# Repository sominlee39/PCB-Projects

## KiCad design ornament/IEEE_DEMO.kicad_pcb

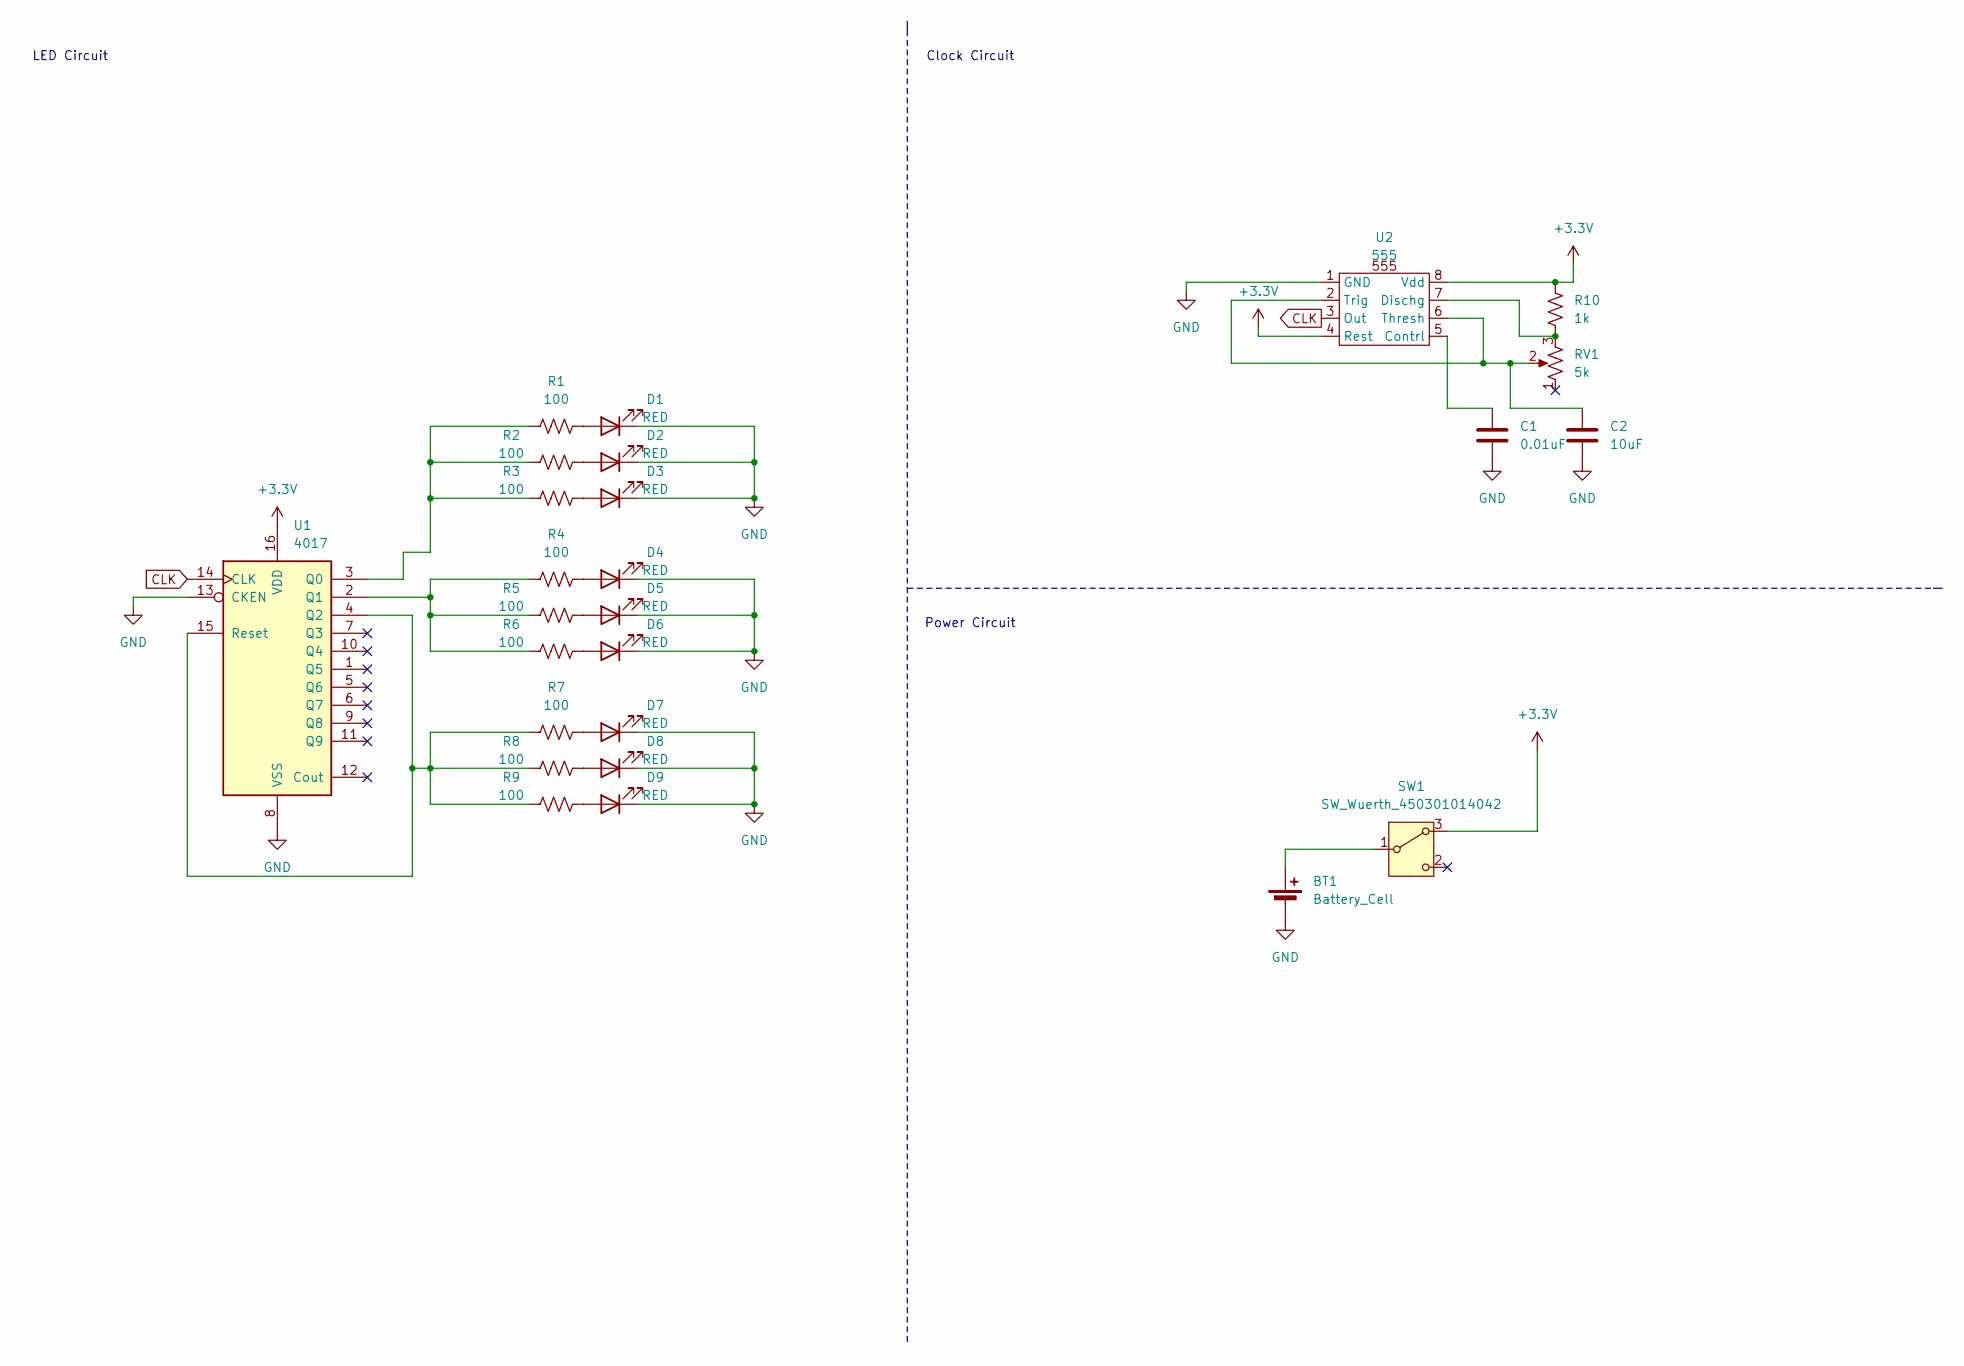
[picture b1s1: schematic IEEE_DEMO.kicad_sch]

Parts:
BT1: Battery_Cell; CR2025TR
C1: 0.01uF; CP_Radial_D5.0mm_P2.50mm
C2: 10uF; CP_Radial_D5.0mm_P2.50mm
D1, D2, D3, D4, D5, D6, D7, D8, D9: RED; LED_D3.0mm
R1, R2, R3, R4, R5, R6, R7, R8, R9: 100; R_0603_1608Metric_Pad0.98x0.95mm_HandSolder
R10: 1k; R_Axial_DIN0207_L6.3mm_D2.5mm_P7.62mm_Horizontal
RV1: 5k; CT6EP504
SW1: SW_Wuerth_450301014042
U1: 4017
U2: 555

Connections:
+3.3V: R10.1, SW1.3 (A), U1.16 (VDD), U2.4 (Rest), U2.8 (Vdd)
CLK: U1.14 (CLK), U2.3 (Out)
GND: BT1.2 (-), C1.2, C2.2, D1.1 (K), D2.1 (K), D3.1 (K), D4.1 (K), D5.1 (K), D6.1 (K), D7.1 (K), D8.1 (K), D9.1 (K), U1.8 (VSS), U1.13 (CKEN), U2.1 (GND)
unnamed: BT1.1 (+), SW1.1 (B)
unnamed: D1.2 (A), R1.2
unnamed: D2.2 (A), R2.2
unnamed: D3.2 (A), R3.2
unnamed: D4.2 (A), R4.2
unnamed: D5.2 (A), R5.2
unnamed: D6.2 (A), R6.2
unnamed: D7.2 (A), R7.2
unnamed: D8.2 (A), R8.2
unnamed: D9.2 (A), R9.2
unnamed: R1.1, R2.1, R3.1, U1.3 (Q0)
unnamed: R4.1, R5.1, R6.1, U1.2 (Q1)
unnamed: R7.1, R8.1, R9.1, U1.4 (Q2), U1.15 (Reset)
unnamed: C1.1, U2.5 (Contrl)
unnamed: R10.2, RV1.3, U2.7 (Dischg)
unnamed: C2.1, RV1.2, U2.2 (Trig), U2.6 (Thresh)

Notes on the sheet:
Power Circuit
Clock Circuit
LED Circuit

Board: 2 copper layers, 26 parts (0 on the bottom side), 19 nets, no tracks yet.

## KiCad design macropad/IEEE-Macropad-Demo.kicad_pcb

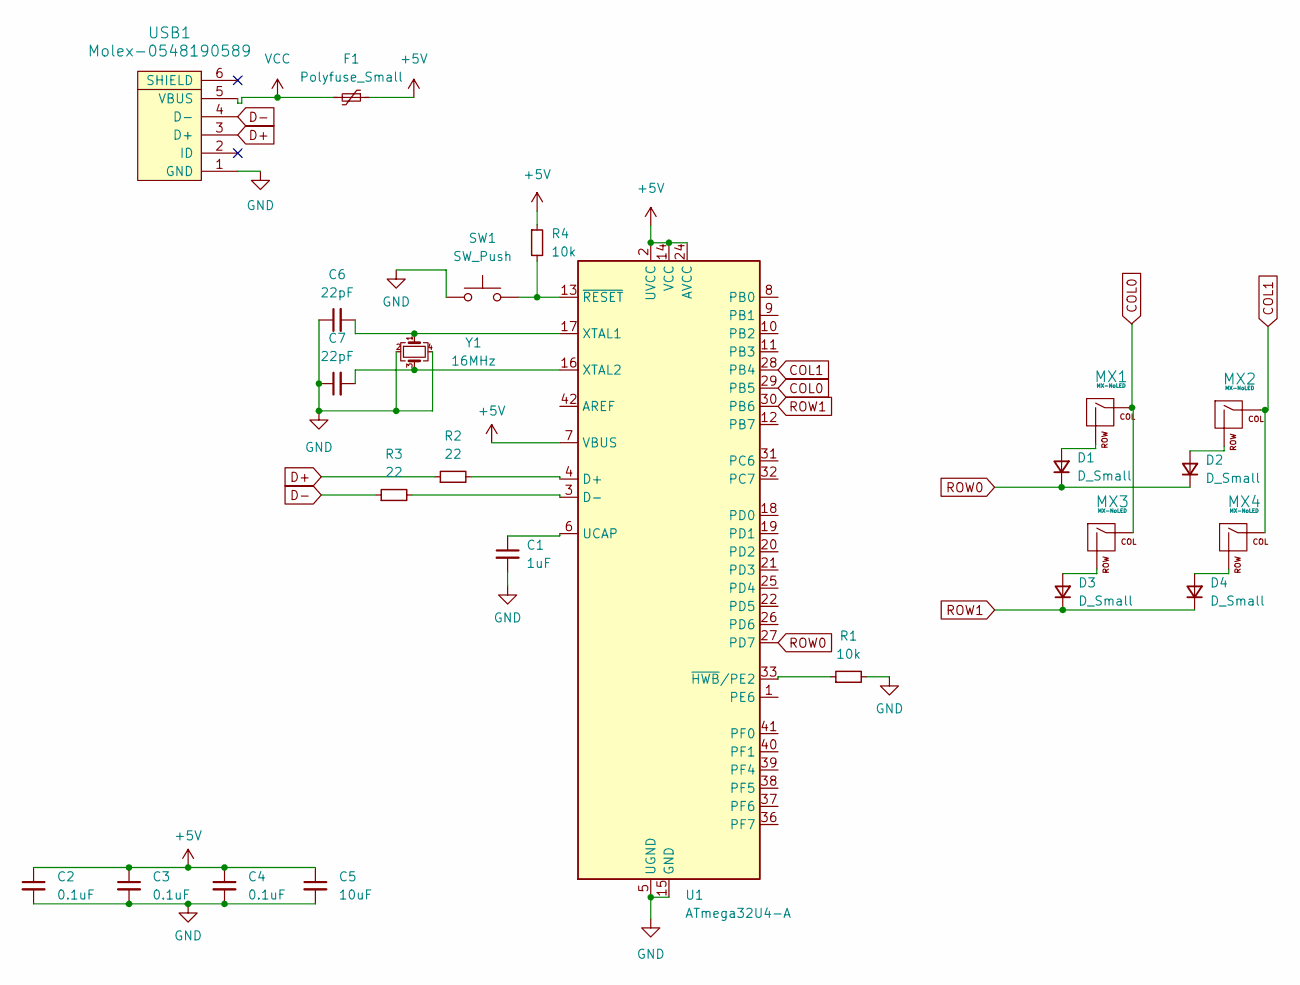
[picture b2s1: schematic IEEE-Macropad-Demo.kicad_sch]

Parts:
C1: 1uF; C_0805_2012Metric
C2, C3, C4: 0.1uF; C_0805_2012Metric
C5: 10uF; C_0805_2012Metric
C6, C7: 22pF; C_0805_2012Metric
D1, D2, D3, D4: D_Small; D_SOD-123
F1: Polyfuse_Small; Fuse_1206_3216Metric
MX1, MX2, MX3, MX4: MX-NoLED; MXOnly-1U-NoLED
R1, R4: 10k; R_0805_2012Metric
R2, R3: 22; R_0805_2012Metric
SW1: SW_Push; SKQG-1155865
U1: ATmega32U4-A; TQFP-44_10x10mm_P0.8mm
USB1: Molex-0548190589
Y1: 16MHz; Crystal_SMD_3225-4Pin_3.2x2.5mm

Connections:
+5V: C2.1, C3.1, C4.1, C5.1, F1.1, R4.1, U1.2 (UVCC), U1.7 (VBUS), U1.14 (VCC), U1.24 (AVCC), U1.34 (VCC), U1.44 (AVCC)
COL0: MX1.1 (COL), MX3.1 (COL), U1.29 (PB5)
COL1: MX2.1 (COL), MX4.1 (COL), U1.28 (PB4)
D+: R2.1, USB1.3 (D+)
D-: R3.1, USB1.4 (D-)
GND: C1.2, C2.2, C3.2, C4.2, C5.2, C6.1, C7.1, R1.2, SW1.1, U1.5 (UGND), U1.15 (GND), U1.23 (GND), U1.35 (GND), U1.43 (GND), USB1.1 (GND), Y1.2, Y1.4
unnamed: D1.2 (A), MX1.2 (ROW)
unnamed: D2.2 (A), MX2.2 (ROW)
unnamed: D3.2 (A), MX3.2 (ROW)
unnamed: D4.2 (A), MX4.2 (ROW)
unnamed: R2.2, U1.4 (D+)
unnamed: R3.2, U1.3 (D-)
unnamed: C1.1, U1.6 (UCAP)
unnamed: C6.2, U1.17 (XTAL1), Y1.1
unnamed: C7.2, U1.16 (XTAL2), Y1.3
unnamed: R1.1, U1.33 (~HWB/PE2)
unnamed: R4.2, SW1.2, U1.13 (~RESET)
ROW0: D1.1 (K), D2.1 (K), U1.27 (PD7)
ROW1: D3.1 (K), D4.1 (K), U1.30 (PB6)
VCC: F1.2, USB1.5 (VBUS)

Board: 2 copper layers, 24 parts (20 on the bottom side), 20 nets, no tracks yet.

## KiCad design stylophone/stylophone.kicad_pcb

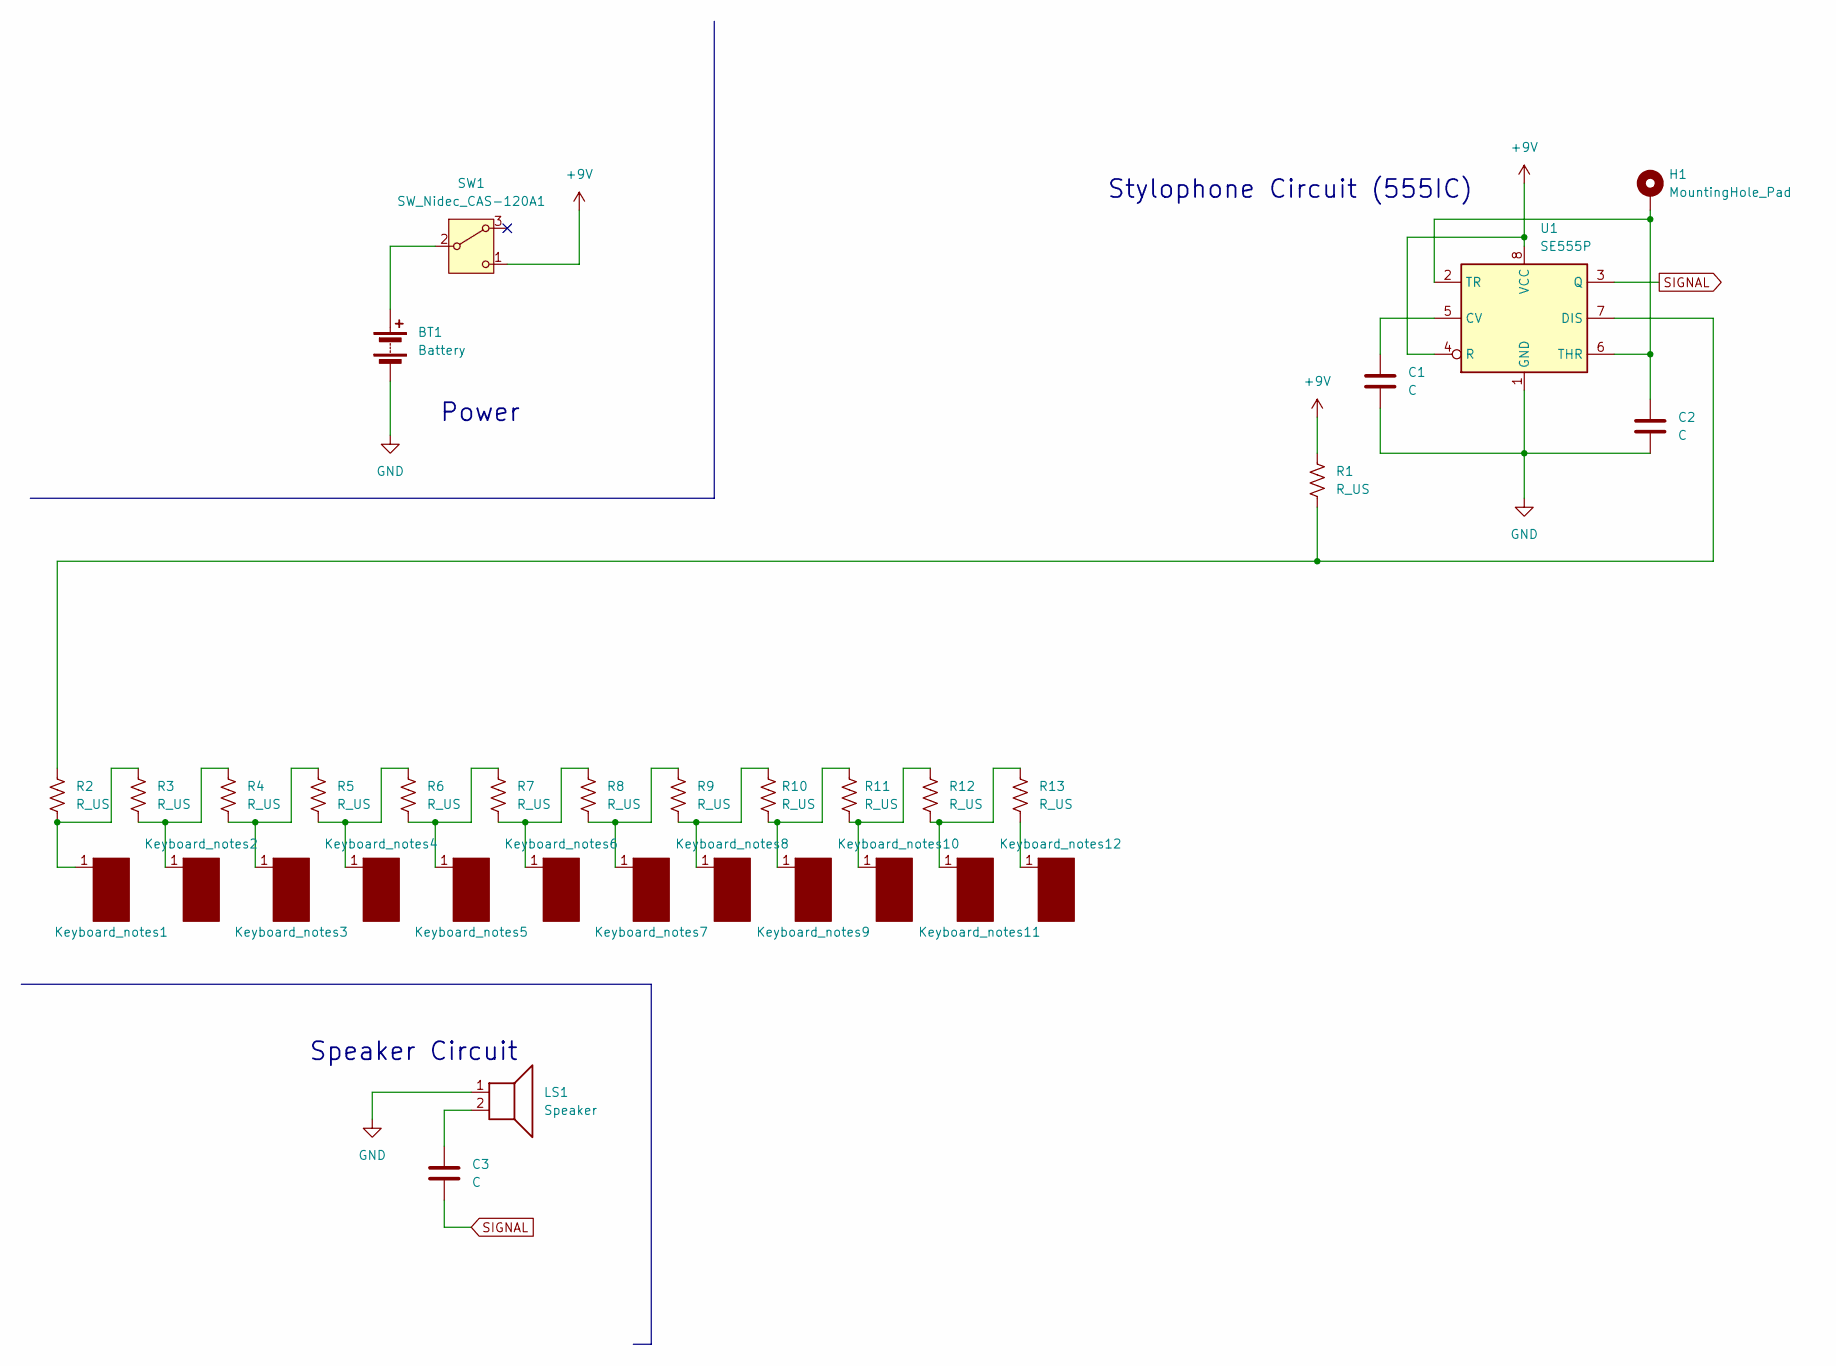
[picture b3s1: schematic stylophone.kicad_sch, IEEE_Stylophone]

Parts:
BT1: Battery; CONN_BH9VPC_MPD
C1, C2, C3: C; CP_Radial_D5.0mm_P2.00mm
H1: MountingHole_Pad; MountingHole_4.3mm_M4_Pad
Keyboard_notes1, Keyboard_notes8: stylophone5
Keyboard_notes2, Keyboard_notes9: stylophone4
Keyboard_notes3, Keyboard_notes5, Keyboard_notes10: stylophone3
Keyboard_notes4: stylophone6
Keyboard_notes6, Keyboard_notes11: stylophone2
Keyboard_notes7, Keyboard_notes12: stylophone1
LS1: Speaker; Buzzer_15x7.5RM7.6
R1, R2, R3, R4, R5, R6, R7, R8, R9, R10, R11, R12, R13: R_US; R_Axial_DIN0207_L6.3mm_D2.5mm_P7.62mm_Horizontal
SW1: SW_Nidec_CAS-120A1; EG1218
U1: SE555P; DIP-8_W7.62mm

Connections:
+9V: R1.1, SW1.1 (C), U1.4 (R), U1.8 (VCC)
GND: BT1.2 (-), C1.2, C2.2, LS1.1, U1.1 (GND)
unnamed: BT1.1 (+), SW1.2 (B)
unnamed: C3.1, LS1.2
unnamed: Keyboard_notes1.1, R2.2, R3.1
unnamed: Keyboard_notes2.1, R3.2, R4.1
unnamed: Keyboard_notes3.1, R4.2, R5.1
unnamed: Keyboard_notes4.1, R5.2, R6.1
unnamed: Keyboard_notes5.1, R6.2, R7.1
unnamed: Keyboard_notes6.1, R7.2, R8.1
unnamed: Keyboard_notes7.1, R8.2, R9.1
unnamed: Keyboard_notes8.1, R9.2, R10.1
unnamed: Keyboard_notes9.1, R10.2, R11.1
unnamed: Keyboard_notes10.1, R11.2, R12.1
unnamed: Keyboard_notes11.1, R12.2, R13.1
unnamed: Keyboard_notes12.1, R13.2
unnamed: C1.1, U1.5 (CV)
unnamed: R1.2, R2.1, U1.7 (DIS)
unnamed: C2.1, H1.1, U1.2 (TR), U1.6 (THR)
SIGNAL: C3.2, U1.3 (Q)

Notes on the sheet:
Power
Stylophone Circuit (555IC)
Speaker Circuit

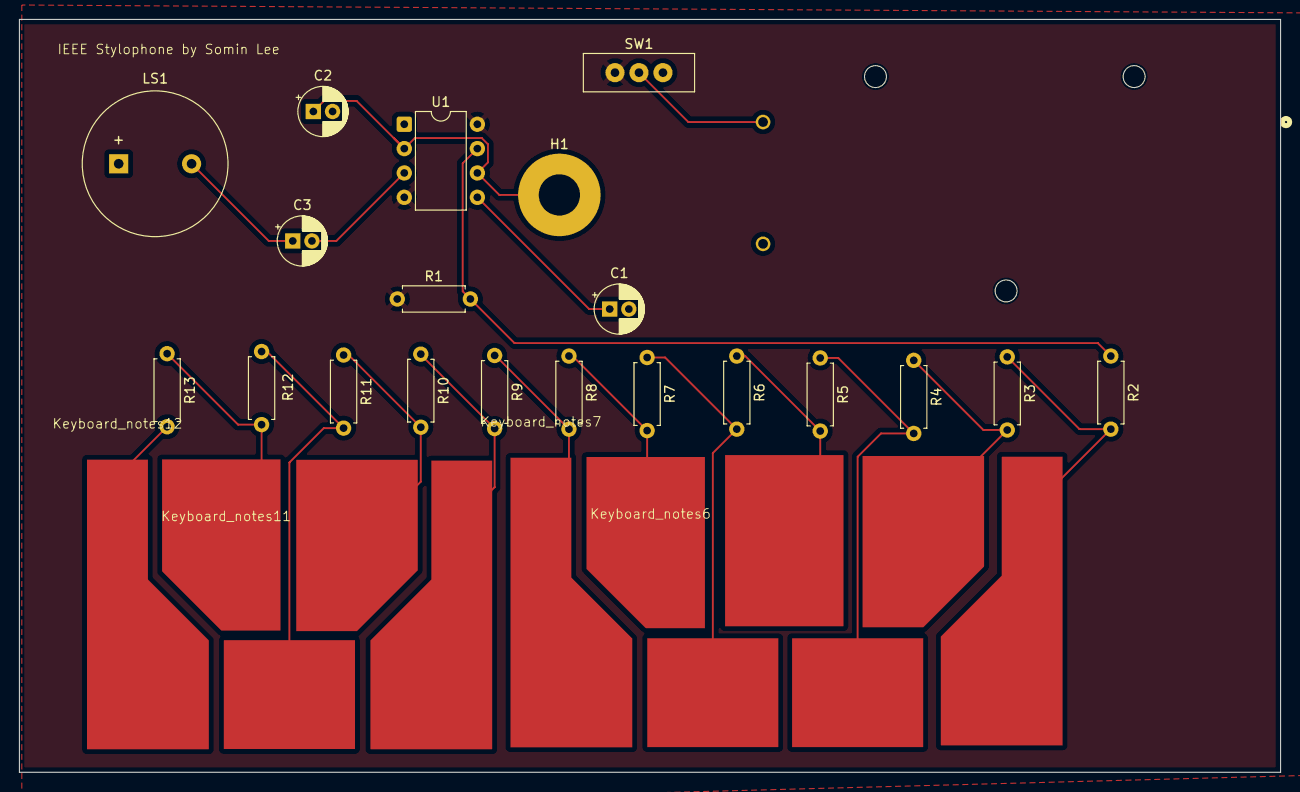
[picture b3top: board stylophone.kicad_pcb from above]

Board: 2 copper layers, 131.5 x 78.5 mm, 33 parts (1 on the bottom side), 20 nets.

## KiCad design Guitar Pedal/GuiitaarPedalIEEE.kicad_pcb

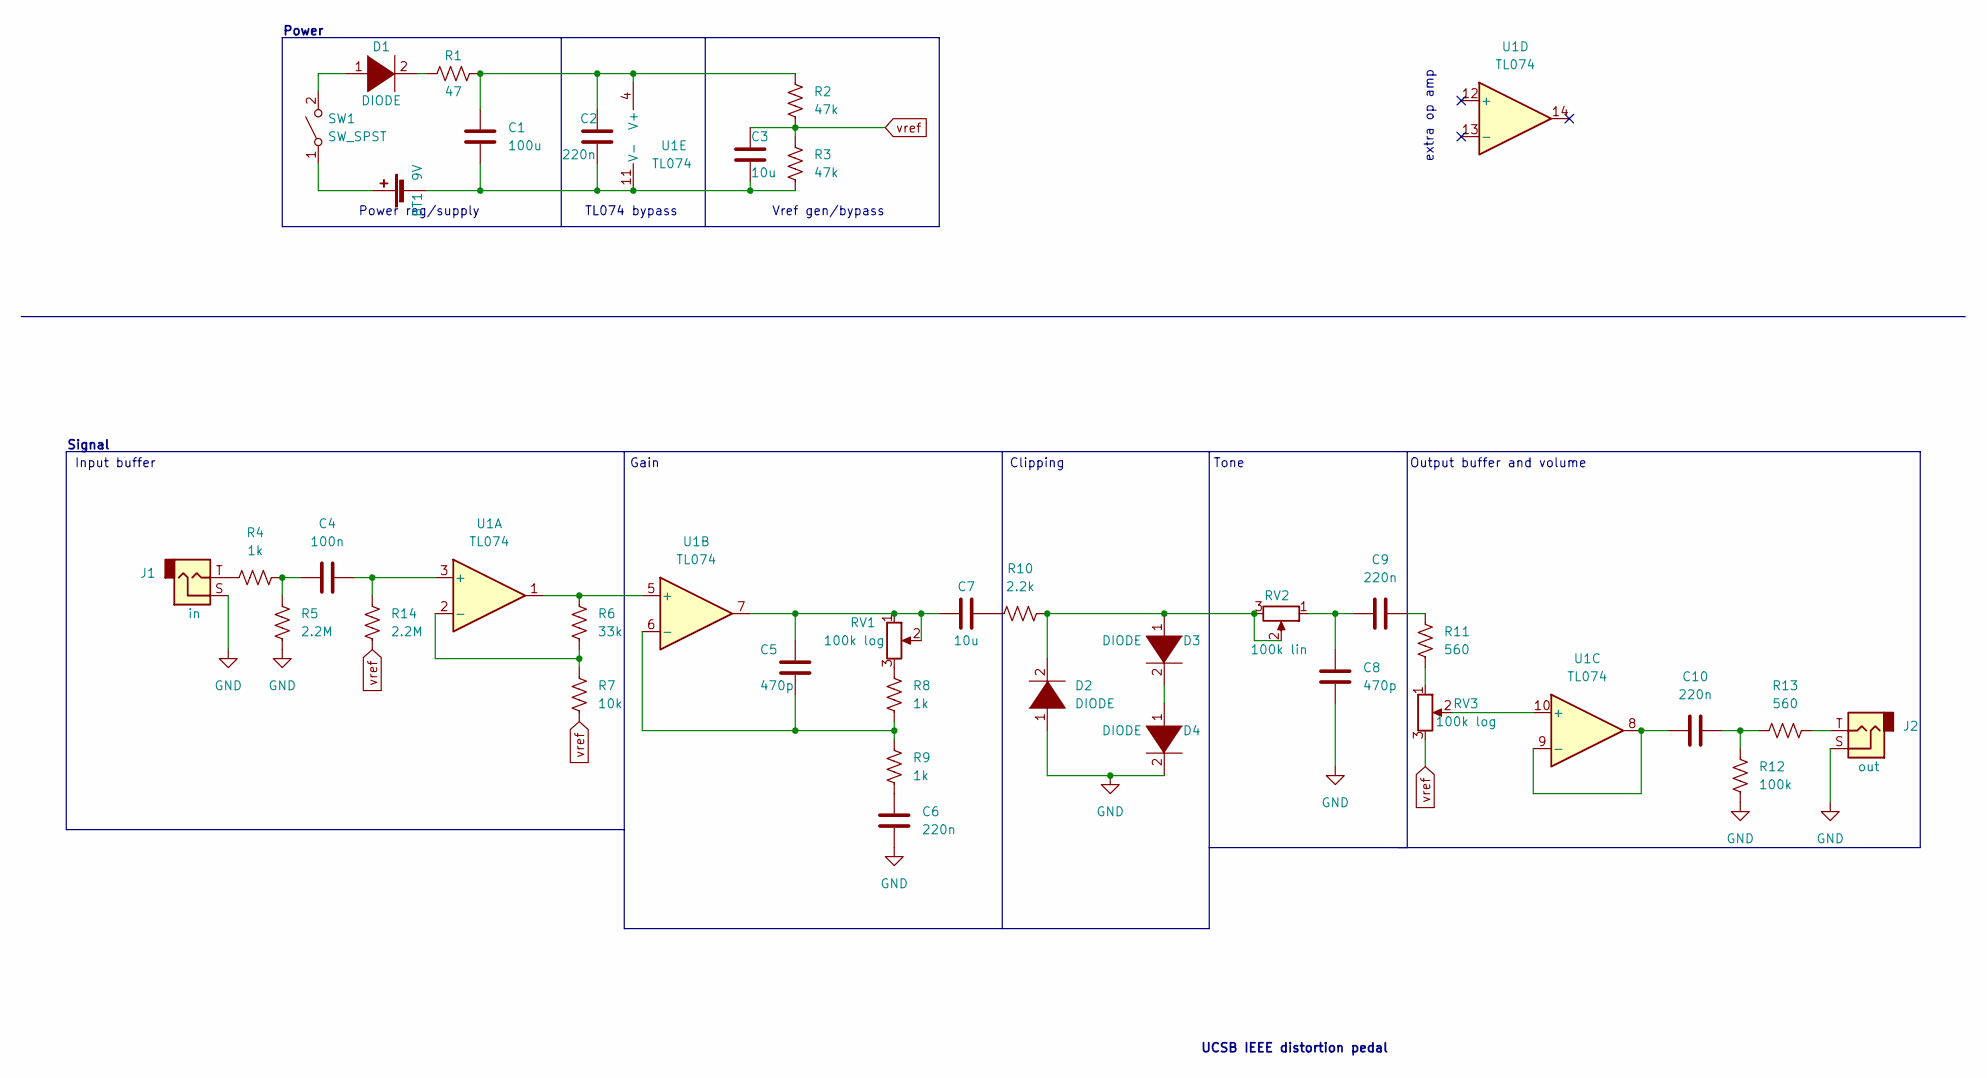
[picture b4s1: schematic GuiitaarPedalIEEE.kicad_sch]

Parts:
BT1: 9V; BatteryHolder_Eagle_12BH611-GR
C1: 100u; CP_Radial_D5.0mm_P2.00mm
C2, C6, C9, C10: 220n; CP_Radial_D5.0mm_P2.00mm
C3, C7: 10u; CP_Radial_D5.0mm_P2.00mm
C4: 100n; CP_Radial_D5.0mm_P2.00mm
C5, C8: 470p; CP_Radial_D5.0mm_P2.00mm
D1, D2, D3, D4: DIODE; D_5W_P10.16mm_Horizontal
J1: in; SWITCHCRAFT_RN111PC
J2: out; SWITCHCRAFT_RN111PC
R1: 47; R_Axial_DIN0207_L6.3mm_D2.5mm_P10.16mm_Horizontal
R2, R3: 47k; R_Axial_DIN0207_L6.3mm_D2.5mm_P10.16mm_Horizontal
R4, R8, R9: 1k; R_Axial_DIN0207_L6.3mm_D2.5mm_P10.16mm_Horizontal
R5, R14: 2.2M; R_Axial_DIN0207_L6.3mm_D2.5mm_P10.16mm_Horizontal
R6: 33k; R_Axial_DIN0207_L6.3mm_D2.5mm_P10.16mm_Horizontal
R7: 10k; R_Axial_DIN0207_L6.3mm_D2.5mm_P10.16mm_Horizontal
R10: 2.2k; R_Axial_DIN0207_L6.3mm_D2.5mm_P10.16mm_Horizontal
R11, R13: 560; R_Axial_DIN0207_L6.3mm_D2.5mm_P10.16mm_Horizontal
R12: 100k; R_Axial_DIN0207_L6.3mm_D2.5mm_P10.16mm_Horizontal
RV1, RV3: 100k log; Potentiometer_Alpha_RD901F-40-00D_Single_Vertical
RV2: 100k lin; Potentiometer_Alpha_RD901F-40-00D_Single_Vertical
SW1: SW_SPST; EG1218
U1: TL074; DIP-14_W7.62mm

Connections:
unnamed: BT1.1 (+), SW1.1 (A)
unnamed: C1.1, C2.1, R1.2, R2.2, U1.4 (V+)
unnamed: C4.1, R4.2, R5.1
unnamed: C4.2, R14.1, U1.3 (+)
unnamed: C5.1, C7.1, RV1.1, RV1.2, U1.7
unnamed: C5.2, R8.2, R9.1, U1.6 (-)
unnamed: C6.1, R9.2
unnamed: C7.2, R10.1
unnamed: C8.2, C9.2, RV2.1
unnamed: C9.1, R11.1
unnamed: C10.1, R12.1, R13.1
unnamed: C10.2, U1.8, U1.9 (-)
unnamed: D1.1 (K), SW1.2 (B)
unnamed: D1.2 (A), R1.1
unnamed: D2.2 (A), D3.1 (K), R10.2, RV2.2, RV2.3
unnamed: D3.2 (A), D4.1 (K)
unnamed: J1.T, R4.1
unnamed: J2.T, R13.2
unnamed: R6.1, U1.1, U1.5 (+)
unnamed: R6.2, R7.1, U1.2 (-)
unnamed: R8.1, RV1.3
unnamed: R11.2, RV3.1
unnamed: RV3.2, U1.10 (+)
vref: C3.1, R2.1, R3.2, R7.2, R14.2, RV3.3

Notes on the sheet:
Gain
Tone
Signal
Clipping
Power
extra op amp
Power reg/supply
TL074 bypass
Input buffer
Output buffer and volume
Vref gen/bypass
UCSB IEEE distortion pedal

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
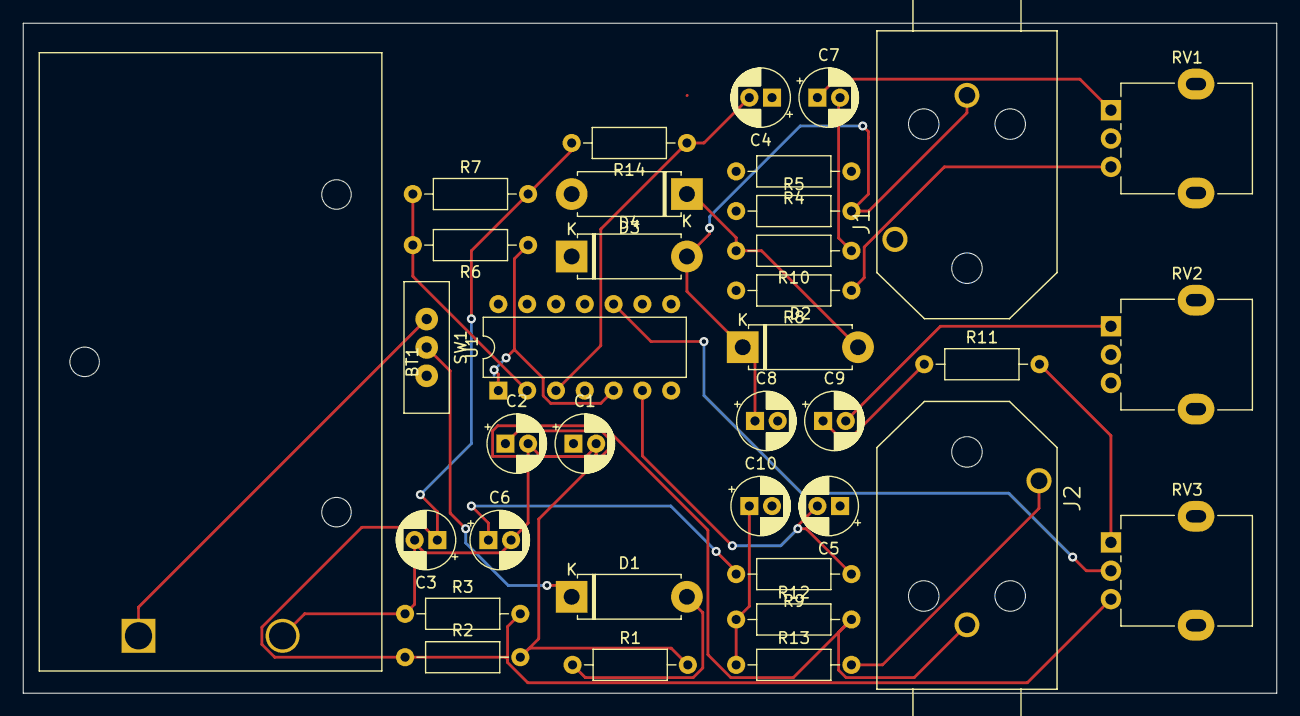
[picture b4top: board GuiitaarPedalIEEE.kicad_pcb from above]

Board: 2 copper layers, 110.5 x 59.1 mm, 36 parts (0 on the bottom side), 25 nets.

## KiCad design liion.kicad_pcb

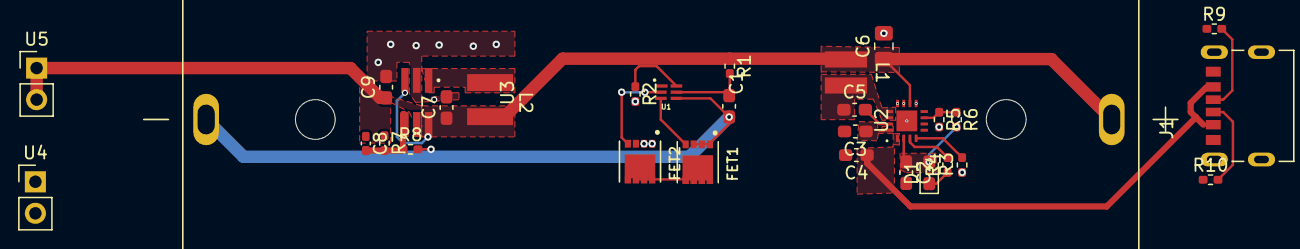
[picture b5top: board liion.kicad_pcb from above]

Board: 2 copper layers, 31 parts (0 on the bottom side), 19 nets.

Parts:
BT1: BK-18650-PC2; BAT_BK-18650-PC2
C1: 0.1uF; C_0603_1608Metric_Pad1.08x0.95mm_HandSolder
C2, C4: 2.2uF; C_0603_1608Metric_Pad1.08x0.95mm_HandSolder
C3, C7, C9: 10uF; C_0603_1608Metric_Pad1.08x0.95mm_HandSolder
C5: 47nF; C_0603_1608Metric_Pad1.08x0.95mm_HandSolder
C6: 10uF; C_0805_2012Metric_Pad1.18x1.45mm_HandSolder
C8: 17.6nF; C_0402_1005Metric_Pad0.74x0.62mm_HandSolder
D1: LED_Small; LED_0603_1608Metric_Pad1.05x0.95mm_HandSolder
FET1, FET2: CSD16406; CSD16406Q3
J1: 2171750001; MOLEX_2171750001
L1: 1uH; L_1212_3030Metric
L2: 1uH; L_1616_4040Metric
R1: 330; R_0402_1005Metric_Pad0.72x0.64mm_HandSolder
R2: 2.2k; R_0402_1005Metric_Pad0.72x0.64mm_HandSolder
R3: 24k; R_0402_1005Metric_Pad0.72x0.64mm_HandSolder
R4: 1.5k; R_0402_1005Metric_Pad0.72x0.64mm_HandSolder
R5, R6: 10k; R_0402_1005Metric_Pad0.72x0.64mm_HandSolder
R7: 9k; R_0402_1005Metric_Pad0.72x0.64mm_HandSolder
R8: 1k; R_0402_1005Metric_Pad0.72x0.64mm_HandSolder
R9, R10: 5.1k; R_0402_1005Metric_Pad0.72x0.64mm_HandSolder
U1: BQ2970; BQ29702DSER
U2: BQ25302
U3: SOT-23-6
U4, U5: 2x1 Port; PinHeader_1x02_P2.54mm_Vertical

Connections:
+5V: C4.1, J1.A9 (VBUS), J1.B9 (VBUS), U2.1 (VBUS)
BAT+: C7.2, C9.2, J1.S1 (SHIELD), J1.S2 (SHIELD), J1.S3 (SHIELD), J1.S4 (SHIELD), U2.9 (VSET), U2.11 (PGND), U2.12 (GND), U2.17 (GND), U3.2 (GND), U4.1, U4.2
BAT-: BT1.+, BT1.-, C1.2, C2.1, C6.1, C6.2, C7.1, C9.1, D1.2 (A), FET1.1 (S1), FET1.2 (S2), FET1.3 (S3), FET2.1 (S1), FET2.2 (S2), FET2.4 (G), L1.2, L2.1, R1.1, R2.1, R2.2, R3.1, R5.2, R6.2, R8.2, U1.2 (COUT), U1.4 (VSS), U1.6 (V-), U2.2 (REGN), U2.10 (BAT), U3.3 (EN), U3.6 (VIN), U5.1, U5.2
GND: C2.2, C3.2, C4.2, FET2.3 (S3), J1.A12 (GND), J1.B12 (GND), R9.1, R10.1
unnamed: D1.1 (K), R4.1
unnamed: FET1.5 (D5), FET1.6 (D6), FET1.7 (D7), FET1.8 (D8), FET2.5 (D5), FET2.6 (D6), FET2.7 (D7), FET2.8 (D8)
unnamed: FET1.4 (G), U1.3 (DOUT)
unnamed: J1.A5 (CC1), R10.2
unnamed: J1.B5 (CC2), R9.2
unnamed: C1.1, R1.2, U1.5 (BAT)
unnamed: C5.2, U2.15 (BTST)
unnamed: R3.2, U2.4 (ICHG)
unnamed: C3.1, U2.16 (PMID)
unnamed: R4.2, U2.3 (STAT)
unnamed: R5.1, R6.1, U2.7 (TS)
unnamed: C8.2, R7.2, R8.1, U3.4 (FB)
unnamed: L2.2, U3.1 (SW)
SW: C5.1, L1.1, U2.13 (SW), U2.14 (SW)
VOUT: C8.1, R7.1, U3.5 (VOUT)
